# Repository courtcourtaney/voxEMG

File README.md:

------------

# VoxEMG (v3.1)

## About
<p>This repository contains information and all the editable project files for the VoxEMG project. VoxEMG is a pre-amplificaton circuit developed specifically for surface electromyography (sEMG) of the small extrinsic laryngeal muscles, but can be used on other muscles. <br>
	
The VoxEMG circuit is an extension of the open-source [EMG Circuit v7.1 (Advancer Technologies)](advancertechnologies.com/p/muscle-sensor-emg-circuitkit-bronze.html), from which other EMG platforms such as the Myoware are derived. VoxEMG is specifically aimed to detect activation of the extrinsic laryngeal muscles in both vocalised and subvocalised singing. High-precision and trimmable resistors are used to ensure noise reduction and the circuit is flexible to be used with different types of electrodes for desired implementation. The EMG signals can then be used in a variety of manners, for instance to relay feedback about the singer's movements during practice. <br>

This is an ongoing body of work with origins in my PhD thesis, [Imagining & Sensing: Understanding and Extending the Vocalist-Voice Relationship Through Biosignal Feedback](https://www.courtneynreed.com/assets/pdf/Reed_PhD_ImaginingSensing.pdf), which contains details on how the circuit and sonified EMG biofeedback has been used in vocal practice. I am always adding more information and designs, so please keep an eye out for updates, new implementations and improvements, and feel free to get in contact at any time regarding the project, what you're working on with it, and anything I can help with at: [c.n.reed@lboro.ac.uk](mailto:c.n.reed@lboro.ac.uk) </p>

## Versions

The schematics and PCB designs have been created in and are editable in [KiCad](http://kicad-pcb.org). Please feel free to adapt them to your needs and share your designs with me if you like!

### v3.1 - eTextile Configuration
[Version Subfolder Here](https://github.com/courtcourtaney/voxEMG/tree/master/VoxEMG-v3.1)

The current version's (v3.1) configuration of the circuit is designed for implementations in wearables, featuring mounting loops in the PCB for securing the board to textile structures and castellated inputs (designed by Adan Benito and Becky Stewart for the [Bela E-textile Capelet](https://oshpark.com/shared_projects/y0oSowUt) on Innovate UK), for conductive thread inputs. <br>

### v3.1.2 - Bela Mini Capelet
[Version Subfolder Here](https://github.com/courtcourtaney/voxEMG/tree/master/VoxEMG-v3.1.2)

<p>The latest PCB design (v3.1.2) features the same circuit implemented to be compatible with the Bela Mini embedded audio platforms. This setup is designed to be plug and play, with EMG being received directly on the A0 and A1 analogue inputs of the Bela Mini, and uses similar Molex connectors for electrode inputs. </p>

The design of this v3.1.2 capelet was supported by [Sound & Music UK's New Voices 2022](https://soundandmusic.org/compose/new-voices-2022/) with vocalist Lou Barnell as part of the piece [<em>To Fly Out in the Heat of Day</em>](https://loubarnell.co.uk/TO-FLY-OUT-IN-THE-HEAT-OF-DAY) - thank you!

## Building the Circuit
If you are interested in getting a VoxEMG board, get in contact - I'm happy to help with any sEMG and vocal projects related projects and I can supply PCBs depending on the project. If you wish to make your own board, it is relatively in-expensive and easy to build the circuit yourself and try it out. A Bill of Materials (BOM) can be found in each version's folder in the file *EMGSensor3.1_bom.xlsx* or listed out below. The setup described here is for single-circuit dual muscle measurement; if you wish to only measure one muscle, you need only use one side of the ICs: <br>

Parts[^1]

* 2x [Texas Instruments OPA1612 op amp](https://www.ti.com/product/OPA1612) <br>
* 5x [Surface cup electrodes](https://www.pulsemedical.co.uk/store/Gold-Reusable-10mm-EEG-Cup-Electrodes-Pack-of-10-Wire-150cm-p79620827)[^2] <br>
* 2x 9V batteries + straps <br>
* Breadboard <br>
* Jumper wires <br>
* Microcontroller of choice or, in our case, a [**Bela**](bela.io)! <br>
* Resistors: <br>
	* 4x 10k Ω 0.1% precison <br>
	* 4x 100k Ω 0.1% precison <br>
	* 2x 100 Ω <br>
	* 2x 1k Ω <br>
	* 6x 10k Ω <br>
	* 2x 100k Ω <br>
	* 2x 150k Ω <br>
* Trimpots/Variable Resistors:<br>
	* 2x 500 Ω <br>
	* 2x 100K Ω <br>
* Capacitors:<br>
	* 1x 0.1 uF ceramic <br>
	* 4x 10 uF ceramic <br>
	* 2x 2.2 nF ceramic <br>
* 2x Schottky 40V 120mA diodes <br><br>

The KiCad project containing the VoxEMG schematics and board layout can be found in the folder for each version *VoxEMG-v3.1,* for the textile-integrated board or *VoxEMG-v3.1.2,* for the Bela Mini capelet, otherwise using the following schematic (v3.1). This schematic depicts use of one side of the ICs - for the second muscle, the connections should be duplicated on the other side. See *VoxEMG-v3.1/EMGSensor3.1.sch* for the full schematic. </p><br>

<!-- *Some notes:* <br> -->
[^1]: Additionally (and especially if you use reusable electrodes), you will need to purchase some adhesive conductive paste (we recommend [Ten20](https://www.pulsemedical.co.uk/store/Ten20-Conductive-Paste-228g-jars-3-pack-10-20-8-p69723951)) and flexible non-woven fabric tape to help secure the electrodes (we use [Hypafix](https://www.bsnmedical.com/products/wound-care-vascular/category-product-search/acute-wound-care/fixation/hypafixr-transparent.html)).

[^2]: These reusable gold-plated silver electrodes use a DIN adaptor intended for use with medical EMG devices; cut these off and you can use either alligator clips to connect these, or solder a male pin to the end of the cable so you can use it in a breadboard or within another cable assembly, such as the Molex connectors implemented in v3.1.2.

<!-- VoxEMG PCB layout          | VoxEMG board
:-------------------------:|:-------------------------:
  |   -->

## Example Use
<p>Electrodes will need to be affixed to the muscle site, for instance on the suprahyoid digastric muscle here.</p><br>

<p>
We use a Bela for collection of voltages from the EMG, and so the code included here is also for Bela - it is fine to use another microcontroller, so long as you're ok with implementing some simple digital filtering. In this case, we use the analog inputs on Bela.</p><br>

Bela handles some additional filtering of the EMG signal, including:<br>
- DC offset removal (from the DC signal introduced in the voltage divider)<br>
- Notch filtering to remove power line interference (**50Hz** UK - keep in mind if you need to change this wherever you are in the world!)<br>

As well, our setup for studies includes:<br>
- Text file output containing voltages over time<br>
- Setup for a button to be added so the vocalist can press during singing, helping with data/audio synchronisation<br>
You can, of course, comment this out (and it's marked as such in the code).

[Example Code Here](https://github.com/courtcourtaney/voxEMG/tree/master/examples)

## Projects Using the VoxEMG

If you have used the circuit or designs for your project, please let us know so we can add you here!

### Vocal Performances & Collaborations

[<em>To Fly Out in the Heat of Day</em>](https://loubarnell.co.uk/TO-FLY-OUT-IN-THE-HEAT-OF-DAY). Lou Barnell. 2023-2024. Performed in the UK & EU ([Based in Sheffield](https://www.theatredeli.co.uk/Event/enddateto-fly-out-in-the-heat-of-the-day)).

### Research Work & Papers
<span style="font-size:2em;"> 

Courtney N. Reed and Andrew P. McPherson. 2023. <em>The Body as Sound: Unpacking Vocal Embodiment through Auditory Biofeedback.</em> In Proceedings of the Seventeenth International Conference on Tangible, Embedded, and Embodied Interaction (TEI '23). Association for Computing Machinery, New York, NY, USA, Article 7, 1–15. https://doi.org/10.1145/3569009.3572738 [[PDF]](https://www.courtneynreed.com/assets/pdf/Reed_TEI23_BodyAsSound.pdf) <br>

Courtney N. Reed, Sophie Skach, Paul Strohmeier, and Andrew P. McPherson. 2022. <em>Singing Knit: Soft Knit Biosensing for Augmenting Vocal Performances.</em> In Proceedings of the Augmented Humans International Conference 2022 (AHs '22). Association for Computing Machinery, New York, NY, USA, 170–183. https://doi.org/10.1145/3519391.3519412 [[PDF]](https://www.courtneynreed.com/assets/pdf/Reed_AHs22_SingingKnit.pdf) <br>

Courtney N. Reed and Andrew P. McPherson. 2021. <em>Surface Electromyography for Sensing Performance Intention and Musical Imagery in Vocalists.</em> In Proceedings of the Fifteenth International Conference on Tangible, Embedded, and Embodied Interaction (TEI '21). Association for Computing Machinery, New York, NY, USA, Article 22, 1–11. https://doi.org/10.1145/3430524.3440641 [[PDF]](https://www.courtneynreed.com/assets/pdf/Reed_TEI21_sEMGPerformance.pdf) <br>

Courtney N. Reed and Andrew P. McPherson. 2020. <em>Surface Electromyography for Direct Vocal Control.</em> In Proceedings of the International Conference on New Interfaces for Musical Expression (NIME), July 21-25, Birmingham, UK, pp. 458–463. Birmingham Conservatoire, Birmingham, UK. https://doi.org/10.5281/zenodo.4813475 [[PDF]](https://www.courtneynreed.com/assets/pdf/Reed_NIME20_VocalsEMG.pdf) <br>
	
</span>

<br>

## Licensing
<p><br /><span xmlns:dct="http://purl.org/dc/terms/" property="dct:title">VoxEMG</span> by <span xmlns:cc="http://creativecommons.org/ns#" property="cc:attributionName">Courtney N. Reed & Andrew P. McPherson</span> is licensed under a <a rel="license" href="http://creativecommons.org/licenses/by-sa/4.0/">Creative Commons Attribution-ShareAlike 4.0 International License</a>. <br>

In the spirit of open-access research, VoxEMG and the circuit/PBC designs included here are are licensed under a Creative Commons Attribtion Sharealike license, or [CC-BY-SA](https://creativecommons.org/licenses/by-sa/3.0/). The information here is free to use and edit, so long as you provide credit and release your resulting work under the same license. This means you are free to edit and use these designs, as long as you agree to supply credit and release your results under the same license. <br>

If you use these designs or reference them, we ask that you please also cite the following papers in your work: <br>

If you want to create a commercial product using the VoxEMG hardware designs and don't want to release it under the same license, you will need a commercial license. Please email me at [c.n.reed@lboro.ac.uk](mailto:c.n.reed@lboro.ac.uk) to enquire further. </p>

```latex
@inproceedings{Reed_AHs22_SingingKnit,
  title = {{Singing Knit: Soft Knit Biosensing for Augmenting Vocal Performances}},
  author = {Reed, Courtney N. and Skach, Sophie and Strohmeier, Paul and McPherson, Andrew P.},
  year = {2022},
  month = mar,
  booktitle = {{Proceedings of the Augmented Humans International Conference 2022}},
  location = {Kashiwa, Chiba, Japan},
  publisher = {Association for Computing Machinery},
  address = {New York, NY, USA},
  series = {AHs '22},
  pages = {170–183},
  doi = {10.1145/3519391.3519412},
  isbn = {9781450396325},
  url = {https://doi.org/10.1145/3519391.3519412},
  numpages = {14},
  keywords = {wearables, Design, singing, music performance, knit, electromyography, fabric sensors, biosignals},
}
```

```latex
@inproceedings{Reed_NIME20_VocalsEMG,
  title = {{Surface Electromyography for Direct Vocal Control}},
  author = {Reed, Courtney N. and McPherson, Andrew},
  year = {2020},
  month = jul,
  booktitle = {{Proceedings of the International Conference on New Interfaces for Musical Expression}},
  publisher = {Birmingham City University},
  address = {Birmingham, UK},
  pages = {458--463},
  doi = {10.5281/zenodo.4813475},
  issn = {2220-4806},
  url = {https://www.nime.org/proceedings/2020/nime2020_paper88.pdf},
  editor = {Michon, Romain and Schroeder, Franziska},
  presentation-video = {https://youtu.be/1nWLgQGNh0g},
}
```

<!-- 
## To-Do List
There's a lot left to done, but at least for this repository, I'm planning on adding more information, including:<br>
- [x] Include editable schematics and PCB design<br>
- [ ] Step-by-step construction of the circuit<br>
- [ ] Walk-through of identifying laryngeal muscles <br>(feel free to contact me and I will help you via Zoom/Skype if you'd like to learn to do this on yourself!)<br>
- [ ] Add example Supercollider interfacing for sonification of signals/fun<br> -->

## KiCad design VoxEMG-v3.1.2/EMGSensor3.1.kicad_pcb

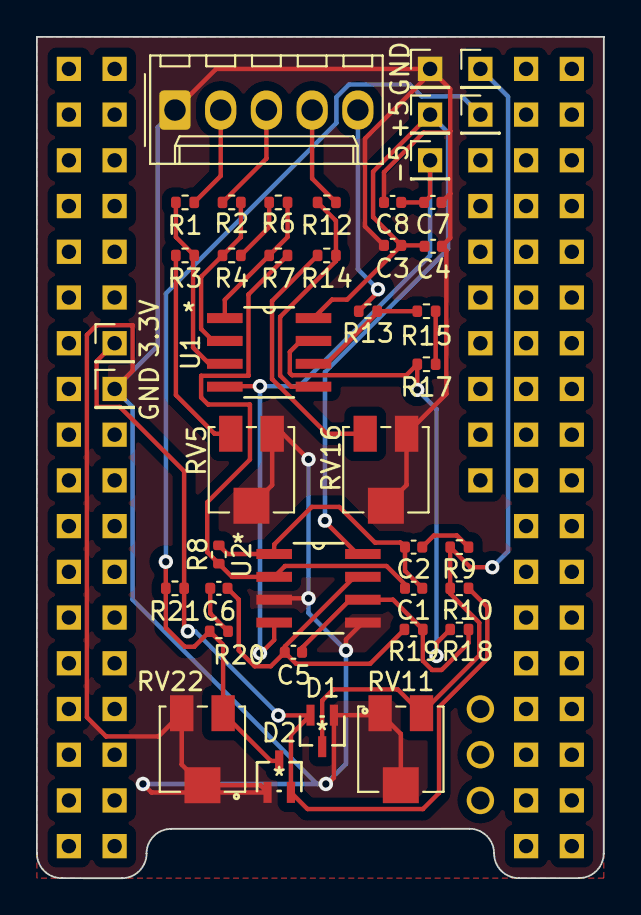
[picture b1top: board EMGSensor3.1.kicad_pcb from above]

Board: 2 copper layers, 31.5 x 46.7 mm, 42 parts (0 on the bottom side), 26 nets.

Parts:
3.3V: +3.3V; PinHeader_1x01_P2.00mm_Vertical
+5: +5V; PinHeader_1x01_P2.00mm_Vertical
-5: -5V; PinHeader_1x01_P2.00mm_Vertical
C1: 2nF; C_0402_1005Metric
C2, C3, C6, C7: 10uF; C_0402_1005Metric
C4, C8: 0.1uF; C_0402_1005Metric
C5: 2.2nF; C_0402_1005Metric
D1, D2: D_Schottky_x2_Serial_AKC; BAS40-04W
GND: BelaGND; PinHeader_1x01_P2.00mm_Vertical
GND#2: BatteryGND; PinHeader_1x01_P2.00mm_Vertical
J1: Conn_01x03_Female; Molex_KK-254_AE-6410-05A_1x05_P2.54mm_Vertical
J5: Out-A; PinHeader_1x01_P2.00mm_Vertical
J6: Out-B; PinHeader_1x01_P2.00mm_Vertical
R1, R2, R7, R12, R13, R18: 10kΩ; R_0402_1005Metric
R3, R4, R10, R14, R15, R21: 100kΩ; R_0402_1005Metric
R6, R17: 100Ω; R_0402_1005Metric
R8, R19: 150kΩ; R_0402_1005Metric
R9, R20: 1kΩ; R_0402_1005Metric
RV5, RV16: 500Ω; Potentiometer_Bourns_3314J_Vertical
RV11, RV22: 100kΩ; Potentiometer_Bourns_3314J_Vertical
U1, U2: OPA1612AID

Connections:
+3.3V: 3.3V.1, D1.2 (K), D2.2 (K), R10.1, R21.1
+5V: +5.1, C3.1, C4.2, U1.8 (V+), U2.8 (V+)
-5V: -5.1, C7.2, C8.2, U1.4 (V-), U2.4 (V-)
/End-Muscle-A: J1.2, R1.2
/End-Muscle-B: J1.4, R12.2
/Mid-Muscle-A: J1.3, R2.2
/Mid-Muscle-B: J1.5, R13.2
GND: C3.2, C4.1, C7.1, C8.1, D1.1 (A), D2.1 (A), GND.1, GND#2.1, J1.1, RV5.1, RV5.2, RV11.2, RV11.3, RV16.1, RV16.2, RV22.2, RV22.3, U2.3 (+), U2.5 (+)
unnamed: C1.2, C2.2, R8.2, U2.1
unnamed: C2.1, R9.1
unnamed: C5.2, C6.2, R19.2, U2.7
unnamed: C6.1, R20.1
unnamed: R3.2, RV5.3
unnamed: R4.1, R6.2
unnamed: R6.1, R7.2, U1.1
unnamed: R14.2, RV16.3
unnamed: R15.1, R17.2
unnamed: R17.1, R18.2, U1.7
unnamed: R1.1, R3.1, U1.3 (+)
unnamed: R2.1, R4.2, U1.2 (-)
unnamed: R12.1, R14.1, U1.5 (+)
unnamed: R13.1, R15.2, U1.6 (-)
unnamed: C1.1, R7.1, R8.1, U2.2 (-)
unnamed: C5.1, R18.1, R19.1, U2.6 (-)
Out-A: D1.3 (common), J5.1, R9.2, R10.2, RV11.1
Out-B: D2.3 (common), J6.1, R20.2, R21.2, RV22.1

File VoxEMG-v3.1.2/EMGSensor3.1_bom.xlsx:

Name | Quantity | Value | Package | Description | Mouser # | Digi-Key # | Datasheet / Notes
U2, U1 | 2 | OPA1612AID | SOIC-8 | OPA1612AID | 595-OPA1612AID
D1, D2 | 2 | Schottky 40V 120mA | SOT-323-3 | BAS40-04 Schottky diode | 771-BAS40-04W-T/R
C1, C5 | 2 | 2.2nF | "0402" | Capacitor ceramic 0402 | 581-04023C222J4T2A
C8, C4 | 2 | 0.1uF | "0402" | Capacitor ceramic 0402 | 581-04023C104KAT2A62
C2, C3, C6, C7 | 4 | 10uF | "0402" | Capacitor ceramic 0402 | 581-0402ZD106MAT2A
R1, R2, R12, R13 | 4 | 10kOhm | "0402" | Resistor 0402 0.1% | 279-CPF-A-0402B10KE
R3, R4, R14, R15 | 4 | 100kOhm | "0402" | Resistor 0402 0.1% | 279-CPF-A0402B100KE1
R6, R17 | 2 | 100Ohm | "0402" | Resistor 0402 | 603-RP0402BRD07100RL
R7, R18 | 6 | 10kOhm | "0402" | Resistor 0402 | 603-RT0402FRE0710KL
R8, R19 | 2 | 150kOhm | "0402" | Resistor 0402 | RT0402FRE07150KL
R9, R20 | 2 | 1kOhm | "0402" | Resistor 0402 | RT0402FRE071KL
R10, R21 | 2 | 100kOhm | "0402" | Resistor 0402 | 603-RT0402FRE07100KL
RV5, RV16 | 2 | 500Ohm | SMD | Bourns 3314J vertical trim potentiometer | 652-3314J-1-501G
RV22, RV11 | 2 | 100kOhm | SMD | Bourns 3314J vertical trim potentiometer | 652-3314J-1-104E
J1 | 2 | Conn 01x05 | Through-hole | Molex K254 22-27-2051 5-pin male header | 538-22-27-2051
J3, J5, J6, J7, J8, J9, J10 | 7 | Connector_PinHeader | Through-hole | 2mm 01x01 vertical pin header | 910-HDR100IMP40MGVTH

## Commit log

2020-05-19 changes to input channels and flipped incorrect button status
2020-07-24 Add files via upload
    add circuit schematics
2020-07-24 Add schematic images
2020-07-24 Update README.md (hopefully for the last time)
2020-07-24 additional comments to render.cpp
2020-08-10 Correction to schematic
    R6 should be 100 ohm to ensure the trimming between the two series can be identical, was incorrectly listed at 500 ohm
2020-08-10 fix R6 values in CAD files
2021-05-11 cleanup, add cad files
2021-05-11 reorganize project folders
2022-07-14 Added VoxBox Pd example
2024-03-05 add v3.1.2, update README
2024-03-05 edits to README
2024-03-06 capelet images, fix capelet spelling

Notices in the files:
parts and their libraries:
Copyright 2016 Accelerated Designs. All rights reserved.
